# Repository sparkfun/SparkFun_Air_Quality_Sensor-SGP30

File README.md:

SparkFun Air Quality Sensor - SGP30 (Qwiic)
========================================

[*SparkFun Air Quality Sensor - SGP30 (Qwiic) (SEN-16531)*](https://www.sparkfun.com/products/16531)

The SGP30 is an Indoor Air Quality Sensor that outputs TVOC (in ppb) and CO<sub>2</sub> (in ppm) values along with raw measurements of H<sub>2</sub> and Ethanol.

Repository Contents
-------------------

* **/Hardware** - Eagle design files (.brd, .sch)
* **/Production** - Production panel files (.brd)

Documentation
--------------
* **[SGP30 Arduino Library](https://github.com/sparkfun/SparkFun_SGP30_Arduino_Library)** - Arduino library for the SparkFun Air Quality Sensor - SGP30.
* **[Hookup Guide](https://learn.sparkfun.com/tutorials/sparkfun-air-quality-sensor---sgp30-qwiic-hookup-guide)** - Basic hookup guide for the SparkFun Air Quality Sensor - SGP30. 
* **[SparkFun Fritzing repo](https://github.com/sparkfun/Fritzing_Parts)** - Fritzing diagrams for SparkFun products.
* **[SparkFun 3D Model repo](https://github.com/sparkfun/3D_Models)** - 3D models of SparkFun products.

Product Versions
----------------
* [SEN-16531](https://www.sparkfun.com/products/16531) - SparkFun initial release.
* [SPX-14813](https://www.sparkfun.com/products/14813) - Original SparkX Release.

License Information
-------------------

This product is _**open source**_! 

Please review the LICENSE.md file for license information. 

If you have any questions or concerns on licensing, please contact technical support on our [SparkFun forums](https://forum.sparkfun.com/viewforum.php?f=152).

Distributed as-is; no warranty is given.

- Your friends at SparkFun.

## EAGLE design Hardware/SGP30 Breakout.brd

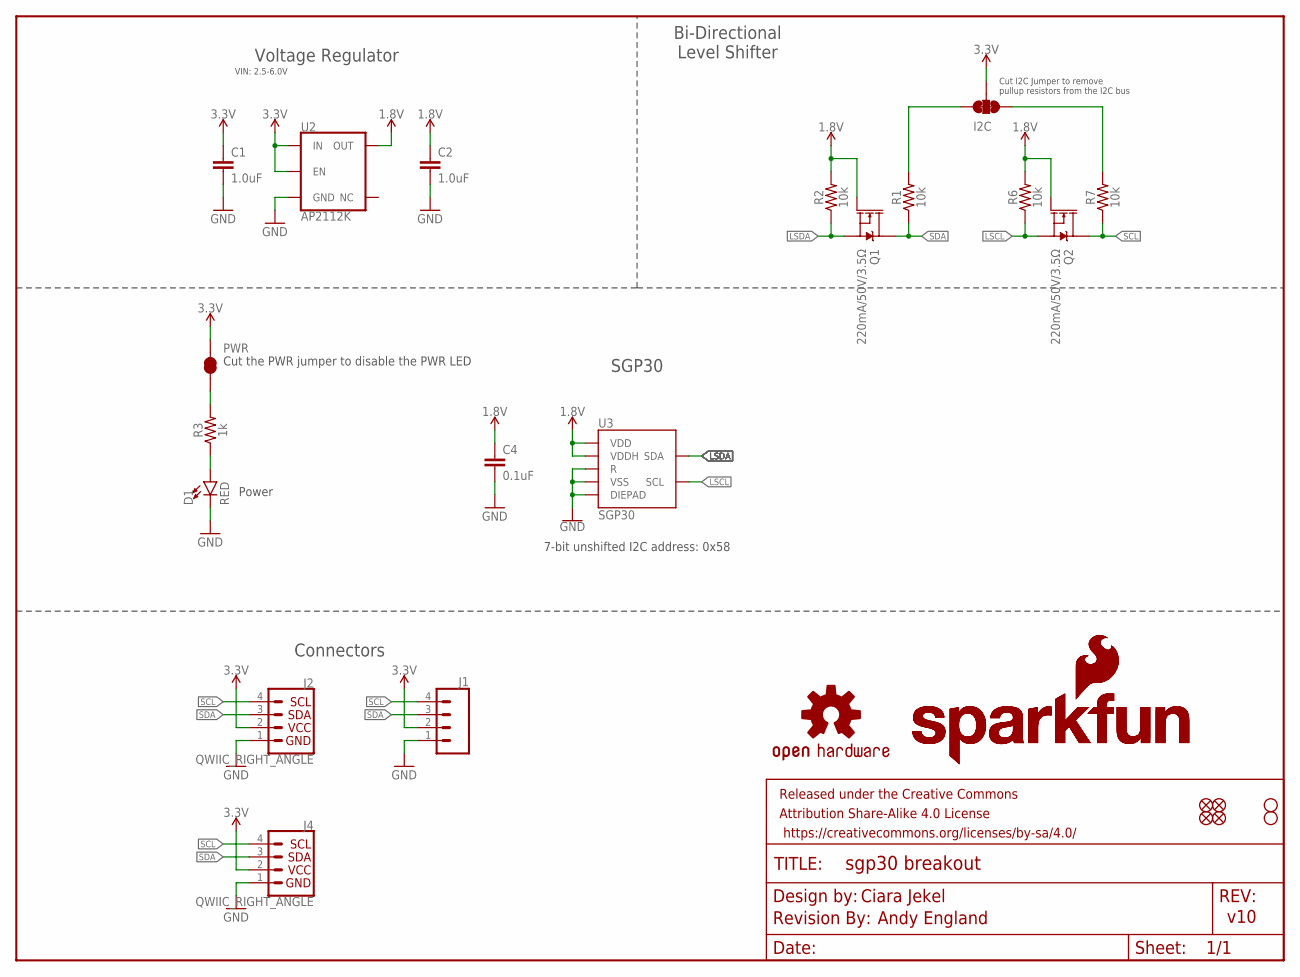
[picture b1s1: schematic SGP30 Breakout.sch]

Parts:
C1, C2: 1.0uF; 0603
C4: 0.1uF; 0603
D1: RED; LED-0603
FRAME1: FRAME-LETTER; CREATIVE_COMMONS
I2C: JUMPER-SMT_3_2-NC_TRACE_SILK; SMT-JUMPER_3_2-NC_TRACE_SILK
J1: CONN_041X04_NO_SILK; 1X04_NO_SILK
J2, J4: QWIIC_RIGHT_ANGLE; JST04_1MM_RA
JP1, JP2, JP5, JP6: FIDUCIALUFIDUCIAL; MICRO-FIDUCIAL
JP3, JP4: STAND-OFF
LOGO2: REVISION
LOGO3, LOGO4: SFE_LOGO_NAME_FLAME.1_INCH; SFE_LOGO_NAME_FLAME_.1
LOGO5: OSHW-LOGOS; OSHW-LOGO-S
PWR: JUMPER-SMT_2_NC_TRACE_SILK; SMT-JUMPER_2_NC_TRACE_SILK
Q1, Q2: 220mA/50V/3.5Ω; SOT23-3
R1, R2, R6, R7: 10k; 0603
R3: 1k; 0603
U2: AP2112K; SOT23-5
U3: SGP30

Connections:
1.8V: C2.1, C4.1, Q1.1 (G), Q2.1 (G), R2.2, R6.2, U2.5 (OUT), U3.1 (VDD), U3.5 (VDDH)
3.3V: C1.1, I2C.2, J1.2, J2.2, J4.2, PWR.2, U2.1 (IN), U2.3 (EN)
GND: C1.2, C2.2, C4.2, D1.C, J1.1, J2.1, J4.1, U2.2 (GND), U3.2 (VSS), U3.4 (R), U3.DIEPAD
LSCL: Q2.2 (S), R6.1, U3.6 (SCL)
LSDA: Q1.2 (S), R2.1, U3.3 (SDA)
unnamed: PWR.1, R3.2
unnamed: I2C.3, R1.2
unnamed: D1.A, R3.1
unnamed: I2C.1, R7.2
SCL: J1.4, J2.4, J4.4, Q2.3 (D), R7.1
SDA: J1.3, J2.3, J4.3, Q1.3 (D), R1.1

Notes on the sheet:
Ciara Jekel
v10
7-bit unshifted I2C address: 0x58
Power
Bi-Directional Level Shifter
Voltage Regulator
SGP30
Connectors
Cut the PWR jumper to disable the PWR LED
Andy England
VIN: 2.5-6.0V
Cut I2C Jumper to remove pullup resistors from the I2C bus

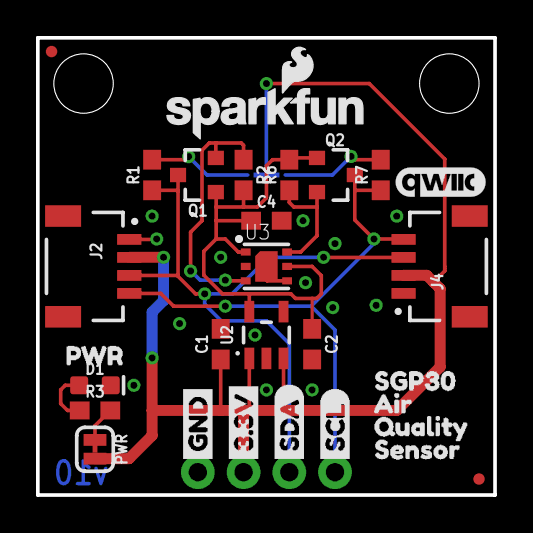
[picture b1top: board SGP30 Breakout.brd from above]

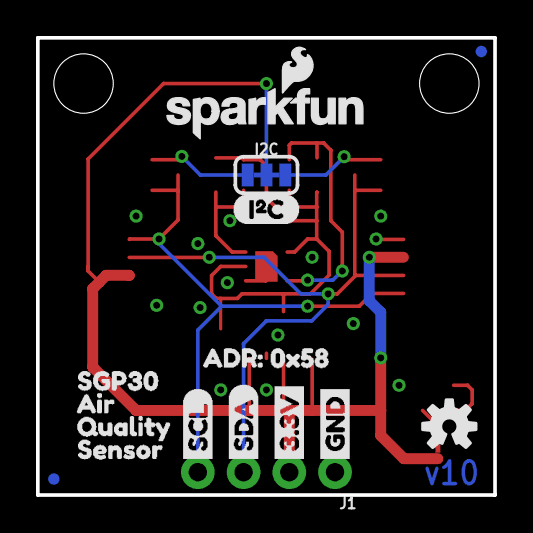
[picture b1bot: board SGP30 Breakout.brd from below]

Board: 2 copper layers, 25.4 x 25.4 mm, 49 parts (16 on the bottom side), 11 nets.

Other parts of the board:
U$1, U$11: _AIR1
U$2, U$12: QUALITY2
U$3, U$22: GND1
U$4, U$21: 3#3V2
U$5, U$27: SDA8
U$6, U$26: SCL9
U$7, U$13: SENSOR3
U$8, U$9: SGP300
U$14: ADR#_0X580
U$15: I2C
U$16: QWIIC_5MM
U$17: PWR_TO

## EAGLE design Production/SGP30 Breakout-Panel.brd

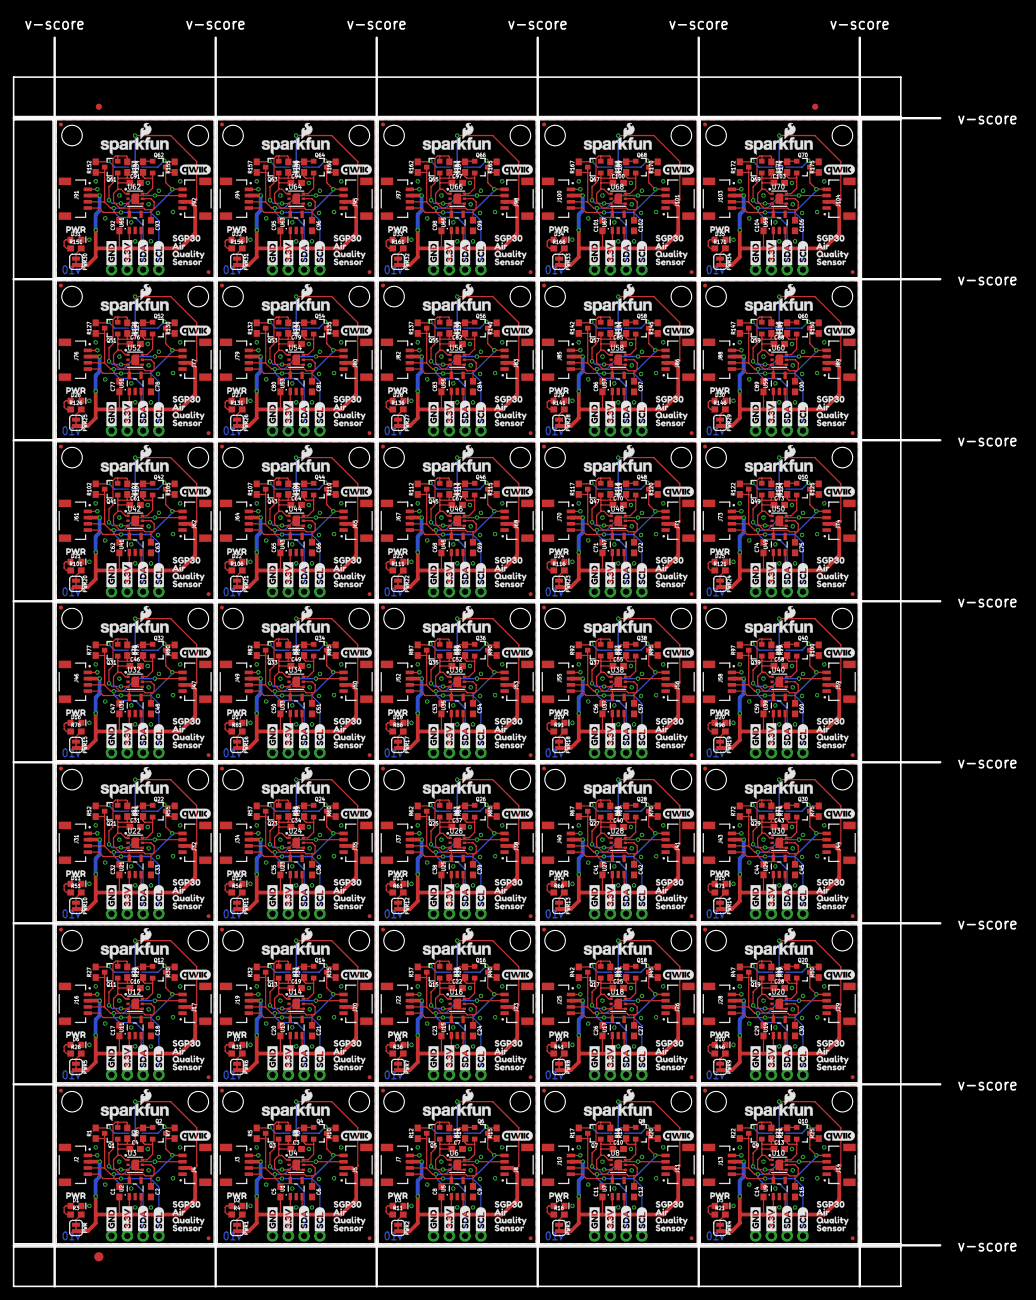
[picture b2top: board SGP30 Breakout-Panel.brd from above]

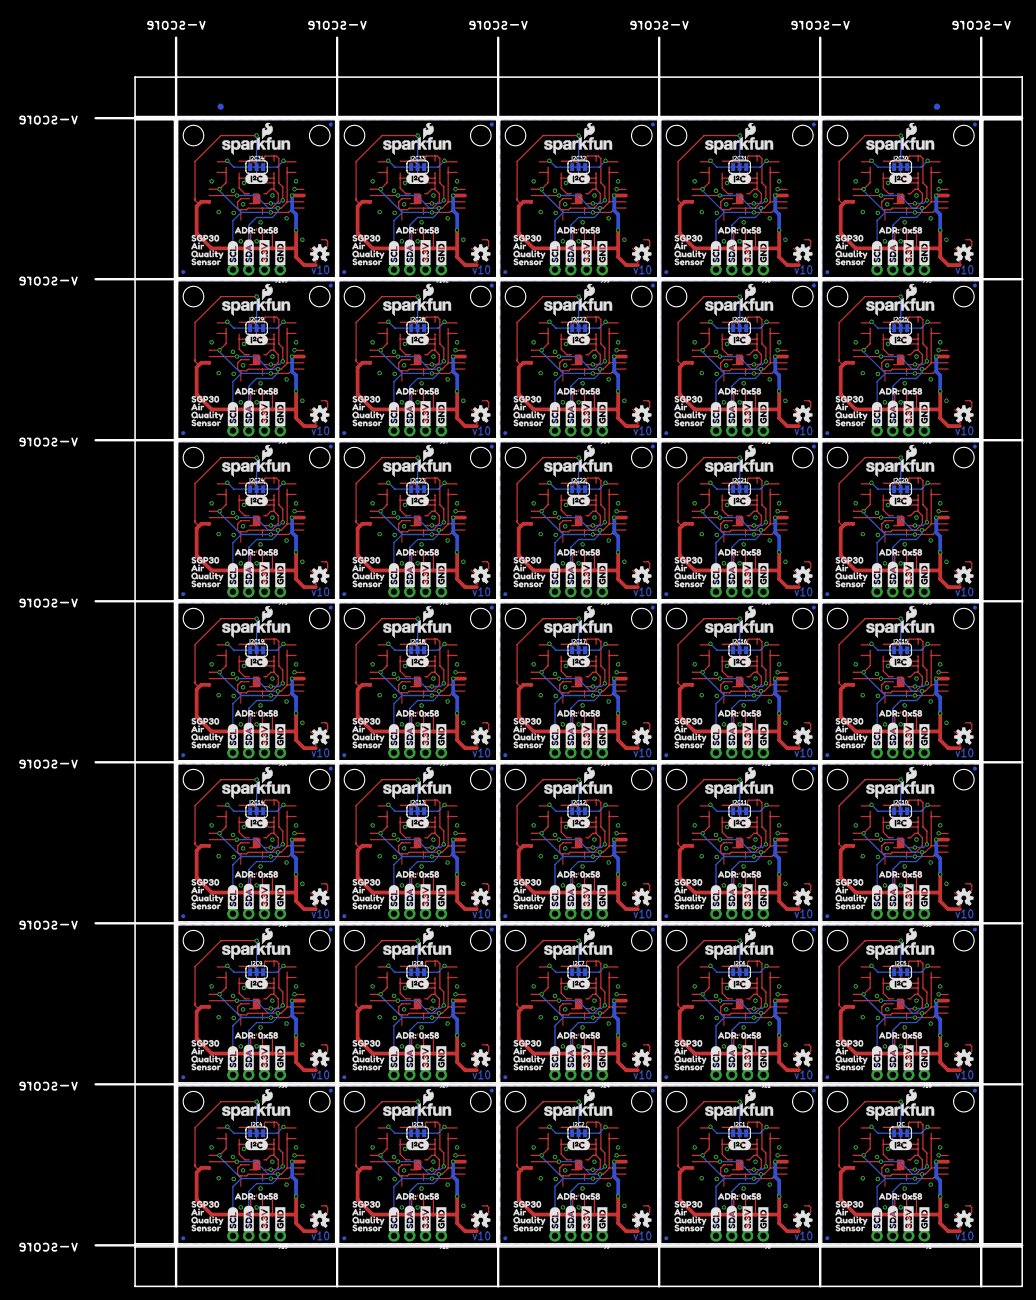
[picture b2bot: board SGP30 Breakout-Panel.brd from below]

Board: 2 copper layers, 149.1 x 200.9 mm, 1685 parts (562 on the bottom side), 385 nets.

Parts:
C1, C2, C5, C6, C8, C9, C11, C12, C14, C15, C17, C18, C20, C21, C23, C24, C26, C27, C29, C30, C32, C33, C35, C36, C38, C39, C41, C42, C44, C45, C47, C48, C50, C51, C53, C54, C56, C57, C59, C60, C62, C63, C65, C66, C68, C69, C71, C72, C74, C75, C77, C78, C80, C81, C83, C84, C86, C87, C89, C90, C92, C93, C95, C96, C98, C99, C101, C102, C104, C105: 1.0uF; 0603
C3, C4, C7, C10, C13, C16, C19, C22, C25, C28, C31, C34, C37, C40, C43, C46, C49, C52, C55, C58, C61, C64, C67, C70, C73, C76, C79, C82, C85, C88, C91, C94, C97, C100, C103: 0.1uF; 0603
D1, D2, D3, D4, D5, D6, D7, D8, D9, D10, D11, D12, D13, D14, D15, D16, D17, D18, D19, D20, D21, D22, D23, D24, D25, D26, D27, D28, D29, D30, D31, D32, D33, D34, D35: RED; LED-0603
E$1, E$2, E$3, E$4: FIDUCIAL-1X2
E$5: FIDUCIAL-1.5X3
I2C, I2C1, I2C2, I2C3, I2C4, I2C5, I2C6, I2C7, I2C8, I2C9, I2C10, I2C11, I2C12, I2C13, I2C14, I2C15, I2C16, I2C17, I2C18, I2C19, I2C20, I2C21, I2C22, I2C23, I2C24, I2C25, I2C26, I2C27, I2C28, I2C29, I2C30, I2C31, I2C32, I2C33, I2C34: JUMPER-SMT_3_2-NC_TRACE_SILK; SMT-JUMPER_3_2-NC_TRACE_SILK
J1, J6, J9, J12, J15, J18, J21, J24, J27, J30, J33, J36, J39, J42, J45, J48, J51, J54, J57, J60, J63, J66, J69, J72, J75, J78, J81, J84, J87, J90, J93, J96, J99, J102, J105: 1X04_NO_SILK
J2, J3, J4, J5, J7, J8, J10, J11, J13, J14, J16, J17, J19, J20, J22, J23, J25, J26, J28, J29, J31, J32, J34, J35, J37, J38, J40, J41, J43, J44, J46, J47, J49, J50, J52, J53, J55, J56, J58, J59, J61, J62, J64, J65, J67, J68, J70, J71, J73, J74, J76, J77, J79, J80, J82, J83, J85, J86, J88, J89, J91, J92, J94, J95, J97, J98, J100, J101, J103, J104: QWIIC_RIGHT_ANGLE; JST04_1MM_RA
JP1, JP2, JP5, JP6, JP9, JP10, JP11, JP12, JP15, JP16, JP17, JP18, JP21, JP22, JP23, JP24, JP27, JP28, JP29, JP30, JP33, JP34, JP35, JP36, JP39, JP40, JP41, JP42, JP45, JP46, JP47, JP48, JP51, JP52, JP53, JP54, JP57, JP58, JP59, JP60, JP63, JP64, JP65, JP66, JP69, JP70, JP71, JP72, JP75, JP76, JP77, JP78, JP81, JP82, JP83, JP84, JP87, JP88, JP89, JP90, JP93, JP94, JP95, JP96, JP99, JP100, JP101, JP102, JP105, JP106, JP107, JP108, JP111, JP112, JP113, JP114, JP117, JP118, JP119, JP120, JP123, JP124, JP125, JP126, JP129, JP130, JP131, JP132, JP135, JP136, JP137, JP138, JP141, JP142, JP143, JP144, JP147, JP148, JP149, JP150, JP153, JP154, JP155, JP156, JP159, JP160, JP161, JP162, JP165, JP166, JP167, JP168, JP171, JP172, JP173, JP174, JP177, JP178, JP179, JP180, JP183, JP184, JP185, JP186, JP189, JP190, JP191, JP192, JP195, JP196, JP197, JP198, JP201, JP202, JP203, JP204, JP207, JP208, JP209, JP210: FIDUCIALUFIDUCIAL; MICRO-FIDUCIAL
JP3, JP4, JP7, JP8, JP13, JP14, JP19, JP20, JP25, JP26, JP31, JP32, JP37, JP38, JP43, JP44, JP49, JP50, JP55, JP56, JP61, JP62, JP67, JP68, JP73, JP74, JP79, JP80, JP85, JP86, JP91, JP92, JP97, JP98, JP103, JP104, JP109, JP110, JP115, JP116, JP121, JP122, JP127, JP128, JP133, JP134, JP139, JP140, JP145, JP146, JP151, JP152, JP157, JP158, JP163, JP164, JP169, JP170, JP175, JP176, JP181, JP182, JP187, JP188, JP193, JP194, JP199, JP200, JP205, JP206: STAND-OFF
LOGO1, LOGO2, LOGO9, LOGO13, LOGO17, LOGO21, LOGO25, LOGO29, LOGO33, LOGO37, LOGO41, LOGO45, LOGO49, LOGO53, LOGO57, LOGO61, LOGO65, LOGO69, LOGO73, LOGO77, LOGO81, LOGO85, LOGO89, LOGO93, LOGO97, LOGO101, LOGO105, LOGO109, LOGO113, LOGO117, LOGO121, LOGO125, LOGO129, LOGO133, LOGO137: REVISION
LOGO3, LOGO4, LOGO6, LOGO7, LOGO10, LOGO11, LOGO14, LOGO15, LOGO18, LOGO19, LOGO22, LOGO23, LOGO26, LOGO27, LOGO30, LOGO31, LOGO34, LOGO35, LOGO38, LOGO39, LOGO42, LOGO43, LOGO46, LOGO47, LOGO50, LOGO51, LOGO54, LOGO55, LOGO58, LOGO59, LOGO62, LOGO63, LOGO66, LOGO67, LOGO70, LOGO71, LOGO74, LOGO75, LOGO78, LOGO79, LOGO82, LOGO83, LOGO86, LOGO87, LOGO90, LOGO91, LOGO94, LOGO95, LOGO98, LOGO99, LOGO102, LOGO103, LOGO106, LOGO107, LOGO110, LOGO111, LOGO114, LOGO115, LOGO118, LOGO119, LOGO122, LOGO123, LOGO126, LOGO127, LOGO130, LOGO131, LOGO134, LOGO135, LOGO138, LOGO139: SFE_LOGO_NAME_FLAME.1_INCH; SFE_LOGO_NAME_FLAME_.1
LOGO5, LOGO8, LOGO12, LOGO16, LOGO20, LOGO24, LOGO28, LOGO32, LOGO36, LOGO40, LOGO44, LOGO48, LOGO52, LOGO56, LOGO60, LOGO64, LOGO68, LOGO72, LOGO76, LOGO80, LOGO84, LOGO88, LOGO92, LOGO96, LOGO100, LOGO104, LOGO108, LOGO112, LOGO116, LOGO120, LOGO124, LOGO128, LOGO132, LOGO136, LOGO140: OSHW-LOGOS; OSHW-LOGO-S
PWR, PWR1, PWR2, PWR3, PWR4, PWR5, PWR6, PWR7, PWR8, PWR9, PWR10, PWR11, PWR12, PWR13, PWR14, PWR15, PWR16, PWR17, PWR18, PWR19, PWR20, PWR21, PWR22, PWR23, PWR24, PWR25, PWR26, PWR27, PWR28, PWR29, PWR30, PWR31, PWR32, PWR33, PWR34: JUMPER-SMT_2_NC_TRACE_SILK; SMT-JUMPER_2_NC_TRACE_SILK
Q1, Q2, Q3, Q4, Q5, Q6, Q7, Q8, Q9, Q10, Q11, Q12, Q13, Q14, Q15, Q16, Q17, Q18, Q19, Q20, Q21, Q22, Q23, Q24, Q25, Q26, Q27, Q28, Q29, Q30, Q31, Q32, Q33, Q34, Q35, Q36, Q37, Q38, Q39, Q40, Q41, Q42, Q43, Q44, Q45, Q46, Q47, Q48, Q49, Q50, Q51, Q52, Q53, Q54, Q55, Q56, Q57, Q58, Q59, Q60, Q61, Q62, Q63, Q64, Q65, Q66, Q67, Q68, Q69, Q70: 220mA/50V/3.5Ω; SOT23-3
R1, R2, R5, R6, R7, R8, R9, R10, R12, R13, R14, R15, R17, R18, R19, R20, R22, R23, R24, R25, R27, R28, R29, R30, R32, R33, R34, R35, R37, R38, R39, R40, R42, R43, R44, R45, R47, R48, R49, R50, R52, R53, R54, R55, R57, R58, R59, R60, R62, R63, R64, R65, R67, R68, R69, R70, R72, R73, R74, R75, R77, R78, R79, R80, R82, R83, R84, R85, R87, R88, R89, R90, R92, R93, R94, R95, R97, R98, R99, R100, R102, R103, R104, R105, R107, R108, R109, R110, R112, R113, R114, R115, R117, R118, R119, R120, R122, R123, R124, R125, R127, R128, R129, R130, R132, R133, R134, R135, R137, R138, R139, R140, R142, R143, R144, R145, R147, R148, R149, R150, R152, R153, R154, R155, R157, R158, R159, R160, R162, R163, R164, R165, R167, R168, R169, R170, R172, R173, R174, R175: 10k; 0603
R3, R4, R11, R16, R21, R26, R31, R36, R41, R46, R51, R56, R61, R66, R71, R76, R81, R86, R91, R96, R101, R106, R111, R116, R121, R126, R131, R136, R141, R146, R151, R156, R161, R166, R171: 1k; 0603
U1, U2, U5, U7, U9, U11, U13, U15, U17, U19, U21, U23, U25, U27, U29, U31, U33, U35, U37, U39, U41, U43, U45, U47, U49, U51, U53, U55, U57, U59, U61, U63, U65, U67, U69: AP2112K; SOT23-5
U3, U4, U6, U8, U10, U12, U14, U16, U18, U20, U22, U24, U26, U28, U30, U32, U34, U36, U38, U40, U42, U44, U46, U48, U50, U52, U54, U56, U58, U60, U62, U64, U66, U68, U70: SGP30
U$1, U$11, U$29, U$34, U$49, U$54, U$69, U$74, U$89, U$94, U$109, U$114, U$129, U$134, U$149, U$154, U$169, U$174, U$189, U$194, U$209, U$214, U$229, U$234, U$249, U$254, U$269, U$274, U$289, U$294, U$309, U$314, U$329, U$334, U$349, U$354, U$369, U$374, U$389, U$394, U$409, U$414, U$429, U$434, U$449, U$454, U$469, U$474, U$489, U$494, U$509, U$514, U$529, U$534, U$549, U$554, U$569, U$574, U$589, U$594, U$609, U$614, U$629, U$634, U$649, U$654, U$669, U$674, U$689, U$694: _AIR1
U$2, U$12, U$30, U$35, U$50, U$55, U$70, U$75, U$90, U$95, U$110, U$115, U$130, U$135, U$150, U$155, U$170, U$175, U$190, U$195, U$210, U$215, U$230, U$235, U$250, U$255, U$270, U$275, U$290, U$295, U$310, U$315, U$330, U$335, U$350, U$355, U$370, U$375, U$390, U$395, U$410, U$415, U$430, U$435, U$450, U$455, U$470, U$475, U$490, U$495, U$510, U$515, U$530, U$535, U$550, U$555, U$570, U$575, U$590, U$595, U$610, U$615, U$630, U$635, U$650, U$655, U$670, U$675, U$690, U$695: QUALITY2
U$3, U$18, U$22, U$23, U$42, U$45, U$62, U$65, U$82, U$85, U$102, U$105, U$122, U$125, U$142, U$145, U$162, U$165, U$182, U$185, U$202, U$205, U$222, U$225, U$242, U$245, U$262, U$265, U$282, U$285, U$302, U$305, U$322, U$325, U$342, U$345, U$362, U$365, U$382, U$385, U$402, U$405, U$422, U$425, U$442, U$445, U$462, U$465, U$482, U$485, U$502, U$505, U$522, U$525, U$542, U$545, U$562, U$565, U$582, U$585, U$602, U$605, U$622, U$625, U$642, U$645, U$662, U$665, U$682, U$685: GND1
U$4, U$10, U$21, U$24, U$41, U$46, U$61, U$66, U$81, U$86, U$101, U$106, U$121, U$126, U$141, U$146, U$161, U$166, U$181, U$186, U$201, U$206, U$221, U$226, U$241, U$246, U$261, U$266, U$281, U$286, U$301, U$306, U$321, U$326, U$341, U$346, U$361, U$366, U$381, U$386, U$401, U$406, U$421, U$426, U$441, U$446, U$461, U$466, U$481, U$486, U$501, U$506, U$521, U$526, U$541, U$546, U$561, U$566, U$581, U$586, U$601, U$606, U$621, U$626, U$641, U$646, U$661, U$666, U$681, U$686: 3#3V2
U$5, U$20, U$25, U$27, U$44, U$47, U$64, U$67, U$84, U$87, U$104, U$107, U$124, U$127, U$144, U$147, U$164, U$167, U$184, U$187, U$204, U$207, U$224, U$227, U$244, U$247, U$264, U$267, U$284, U$287, U$304, U$307, U$324, U$327, U$344, U$347, U$364, U$367, U$384, U$387, U$404, U$407, U$424, U$427, U$444, U$447, U$464, U$467, U$484, U$487, U$504, U$507, U$524, U$527, U$544, U$547, U$564, U$567, U$584, U$587, U$604, U$607, U$624, U$627, U$644, U$647, U$664, U$667, U$684, U$687: SDA8
U$6, U$19, U$26, U$28, U$43, U$48, U$63, U$68, U$83, U$88, U$103, U$108, U$123, U$128, U$143, U$148, U$163, U$168, U$183, U$188, U$203, U$208, U$223, U$228, U$243, U$248, U$263, U$268, U$283, U$288, U$303, U$308, U$323, U$328, U$343, U$348, U$363, U$368, U$383, U$388, U$403, U$408, U$423, U$428, U$443, U$448, U$463, U$468, U$483, U$488, U$503, U$508, U$523, U$528, U$543, U$548, U$563, U$568, U$583, U$588, U$603, U$608, U$623, U$628, U$643, U$648, U$663, U$668, U$683, U$688: SCL9
U$7, U$13, U$31, U$36, U$51, U$56, U$71, U$76, U$91, U$96, U$111, U$116, U$131, U$136, U$151, U$156, U$171, U$176, U$191, U$196, U$211, U$216, U$231, U$236, U$251, U$256, U$271, U$276, U$291, U$296, U$311, U$316, U$331, U$336, U$351, U$356, U$371, U$376, U$391, U$396, U$411, U$416, U$431, U$436, U$451, U$456, U$471, U$476, U$491, U$496, U$511, U$516, U$531, U$536, U$551, U$556, U$571, U$576, U$591, U$596, U$611, U$616, U$631, U$636, U$651, U$656, U$671, U$676, U$691, U$696: SENSOR3
U$8, U$9, U$32, U$33, U$52, U$53, U$72, U$73, U$92, U$93, U$112, U$113, U$132, U$133, U$152, U$153, U$172, U$173, U$192, U$193, U$212, U$213, U$232, U$233, U$252, U$253, U$272, U$273, U$292, U$293, U$312, U$313, U$332, U$333, U$352, U$353, U$372, U$373, U$392, U$393, U$412, U$413, U$432, U$433, U$452, U$453, U$472, U$473, U$492, U$493, U$512, U$513, U$532, U$533, U$552, U$553, U$572, U$573, U$592, U$593, U$612, U$613, U$632, U$633, U$652, U$653, U$672, U$673, U$692, U$693: SGP300
U$14, U$37, U$57, U$77, U$97, U$117, U$137, U$157, U$177, U$197, U$217, U$237, U$257, U$277, U$297, U$317, U$337, U$357, U$377, U$397, U$417, U$437, U$457, U$477, U$497, U$517, U$537, U$557, U$577, U$597, U$617, U$637, U$657, U$677, U$697: ADR#_0X580
U$15, U$38, U$58, U$78, U$98, U$118, U$138, U$158, U$178, U$198, U$218, U$238, U$258, U$278, U$298, U$318, U$338, U$358, U$378, U$398, U$418, U$438, U$458, U$478, U$498, U$518, U$538, U$558, U$578, U$598, U$618, U$638, U$658, U$678, U$698: I2C
U$16, U$39, U$59, U$79, U$99, U$119, U$139, U$159, U$179, U$199, U$219, U$239, U$259, U$279, U$299, U$319, U$339, U$359, U$379, U$399, U$419, U$439, U$459, U$479, U$499, U$519, U$539, U$559, U$579, U$599, U$619, U$639, U$659, U$679, U$699: QWIIC_5MM
U$17, U$40, U$60, U$80, U$100, U$120, U$140, U$160, U$180, U$200, U$220, U$240, U$260, U$280, U$300, U$320, U$340, U$360, U$380, U$400, U$420, U$440, U$460, U$480, U$500, U$520, U$540, U$560, U$580, U$600, U$620, U$640, U$660, U$680, U$700: PWR_TO

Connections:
1.8V: C2.1, C4.1, Q1.1, Q2.1, R2.2, R6.2, U2.5, U3.1, U3.5
1.8V1: C3.1, C6.1, Q3.1, Q4.1, R8.2, R9.2, U1.5, U4.1, U4.5
1.8V2: C7.1, C9.1, Q5.1, Q6.1, R13.2, R14.2, U5.5, U6.1, U6.5
1.8V3: C10.1, C12.1, Q7.1, Q8.1, R18.2, R19.2, U7.5, U8.1, U8.5
1.8V4: C13.1, C15.1, Q9.1, Q10.1, R23.2, R24.2, U9.5, U10.1, U10.5
1.8V5: C16.1, C18.1, Q11.1, Q12.1, R28.2, R29.2, U11.5, U12.1, U12.5
1.8V6: C19.1, C21.1, Q13.1, Q14.1, R33.2, R34.2, U13.5, U14.1, U14.5
1.8V7: C22.1, C24.1, Q15.1, Q16.1, R38.2, R39.2, U15.5, U16.1, U16.5
1.8V8: C25.1, C27.1, Q17.1, Q18.1, R43.2, R44.2, U17.5, U18.1, U18.5
1.8V9: C28.1, C30.1, Q19.1, Q20.1, R48.2, R49.2, U19.5, U20.1, U20.5
1.8V10: C31.1, C33.1, Q21.1, Q22.1, R53.2, R54.2, U21.5, U22.1, U22.5
1.8V11: C34.1, C36.1, Q23.1, Q24.1, R58.2, R59.2, U23.5, U24.1, U24.5
1.8V12: C37.1, C39.1, Q25.1, Q26.1, R63.2, R64.2, U25.5, U26.1, U26.5
1.8V13: C40.1, C42.1, Q27.1, Q28.1, R68.2, R69.2, U27.5, U28.1, U28.5
1.8V14: C43.1, C45.1, Q29.1, Q30.1, R73.2, R74.2, U29.5, U30.1, U30.5
1.8V15: C46.1, C48.1, Q31.1, Q32.1, R78.2, R79.2, U31.5, U32.1, U32.5
1.8V16: C49.1, C51.1, Q33.1, Q34.1, R83.2, R84.2, U33.5, U34.1, U34.5
1.8V17: C52.1, C54.1, Q35.1, Q36.1, R88.2, R89.2, U35.5, U36.1, U36.5
1.8V18: C55.1, C57.1, Q37.1, Q38.1, R93.2, R94.2, U37.5, U38.1, U38.5
1.8V19: C58.1, C60.1, Q39.1, Q40.1, R98.2, R99.2, U39.5, U40.1, U40.5
1.8V20: C61.1, C63.1, Q41.1, Q42.1, R103.2, R104.2, U41.5, U42.1, U42.5
1.8V21: C64.1, C66.1, Q43.1, Q44.1, R108.2, R109.2, U43.5, U44.1, U44.5
1.8V22: C67.1, C69.1, Q45.1, Q46.1, R113.2, R114.2, U45.5, U46.1, U46.5
1.8V23: C70.1, C72.1, Q47.1, Q48.1, R118.2, R119.2, U47.5, U48.1, U48.5
1.8V24: C73.1, C75.1, Q49.1, Q50.1, R123.2, R124.2, U49.5, U50.1, U50.5
1.8V25: C76.1, C78.1, Q51.1, Q52.1, R128.2, R129.2, U51.5, U52.1, U52.5
1.8V26: C79.1, C81.1, Q53.1, Q54.1, R133.2, R134.2, U53.5, U54.1, U54.5
1.8V27: C82.1, C84.1, Q55.1, Q56.1, R138.2, R139.2, U55.5, U56.1, U56.5
1.8V28: C85.1, C87.1, Q57.1, Q58.1, R143.2, R144.2, U57.5, U58.1, U58.5
1.8V29: C88.1, C90.1, Q59.1, Q60.1, R148.2, R149.2, U59.5, U60.1, U60.5
1.8V30: C91.1, C93.1, Q61.1, Q62.1, R153.2, R154.2, U61.5, U62.1, U62.5
1.8V31: C94.1, C96.1, Q63.1, Q64.1, R158.2, R159.2, U63.5, U64.1, U64.5
1.8V32: C97.1, C99.1, Q65.1, Q66.1, R163.2, R164.2, U65.5, U66.1, U66.5
1.8V33: C100.1, C102.1, Q67.1, Q68.1, R168.2, R169.2, U67.5, U68.1, U68.5
1.8V34: C103.1, C105.1, Q69.1, Q70.1, R173.2, R174.2, U69.5, U70.1, U70.5
3.3V: C1.1, I2C.2, J1.2, J2.2, J4.2, PWR.2, U2.1, U2.3
3.3V1: C5.1, I2C1.2, J3.2, J5.2, J6.2, PWR1.2, U1.1, U1.3
3.3V2: C8.1, I2C2.2, J7.2, J8.2, J9.2, PWR2.2, U5.1, U5.3
3.3V3: C11.1, I2C3.2, J10.2, J11.2, J12.2, PWR3.2, U7.1, U7.3
3.3V4: C14.1, I2C4.2, J13.2, J14.2, J15.2, PWR4.2, U9.1, U9.3
3.3V5: C17.1, I2C5.2, J16.2, J17.2, J18.2, PWR5.2, U11.1, U11.3
3.3V6: C20.1, I2C6.2, J19.2, J20.2, J21.2, PWR6.2, U13.1, U13.3
3.3V7: C23.1, I2C7.2, J22.2, J23.2, J24.2, PWR7.2, U15.1, U15.3
3.3V8: C26.1, I2C8.2, J25.2, J26.2, J27.2, PWR8.2, U17.1, U17.3
3.3V9: C29.1, I2C9.2, J28.2, J29.2, J30.2, PWR9.2, U19.1, U19.3
3.3V10: C32.1, I2C10.2, J31.2, J32.2, J33.2, PWR10.2, U21.1, U21.3
3.3V11: C35.1, I2C11.2, J34.2, J35.2, J36.2, PWR11.2, U23.1, U23.3
3.3V12: C38.1, I2C12.2, J37.2, J38.2, J39.2, PWR12.2, U25.1, U25.3
3.3V13: C41.1, I2C13.2, J40.2, J41.2, J42.2, PWR13.2, U27.1, U27.3
3.3V14: C44.1, I2C14.2, J43.2, J44.2, J45.2, PWR14.2, U29.1, U29.3
3.3V15: C47.1, I2C15.2, J46.2, J47.2, J48.2, PWR15.2, U31.1, U31.3
3.3V16: C50.1, I2C16.2, J49.2, J50.2, J51.2, PWR16.2, U33.1, U33.3
3.3V17: C53.1, I2C17.2, J52.2, J53.2, J54.2, PWR17.2, U35.1, U35.3
3.3V18: C56.1, I2C18.2, J55.2, J56.2, J57.2, PWR18.2, U37.1, U37.3
3.3V19: C59.1, I2C19.2, J58.2, J59.2, J60.2, PWR19.2, U39.1, U39.3
3.3V20: C62.1, I2C20.2, J61.2, J62.2, J63.2, PWR20.2, U41.1, U41.3
3.3V21: C65.1, I2C21.2, J64.2, J65.2, J66.2, PWR21.2, U43.1, U43.3
3.3V22: C68.1, I2C22.2, J67.2, J68.2, J69.2, PWR22.2, U45.1, U45.3
3.3V23: C71.1, I2C23.2, J70.2, J71.2, J72.2, PWR23.2, U47.1, U47.3
3.3V24: C74.1, I2C24.2, J73.2, J74.2, J75.2, PWR24.2, U49.1, U49.3
3.3V25: C77.1, I2C25.2, J76.2, J77.2, J78.2, PWR25.2, U51.1, U51.3
3.3V26: C80.1, I2C26.2, J79.2, J80.2, J81.2, PWR26.2, U53.1, U53.3
3.3V27: C83.1, I2C27.2, J82.2, J83.2, J84.2, PWR27.2, U55.1, U55.3
3.3V28: C86.1, I2C28.2, J85.2, J86.2, J87.2, PWR28.2, U57.1, U57.3
3.3V29: C89.1, I2C29.2, J88.2, J89.2, J90.2, PWR29.2, U59.1, U59.3
3.3V30: C92.1, I2C30.2, J91.2, J92.2, J93.2, PWR30.2, U61.1, U61.3
3.3V31: C95.1, I2C31.2, J94.2, J95.2, J96.2, PWR31.2, U63.1, U63.3
3.3V32: C98.1, I2C32.2, J97.2, J98.2, J99.2, PWR32.2, U65.1, U65.3
3.3V33: C101.1, I2C33.2, J100.2, J101.2, J102.2, PWR33.2, U67.1, U67.3
3.3V34: C104.1, I2C34.2, J103.2, J104.2, J105.2, PWR34.2, U69.1, U69.3
GND: C1.2, C2.2, C4.2, D1.C, J1.1, J2.1, J4.1, U2.2, U3.2, U3.4, U3.DIEPAD
GND1: C3.2, C5.2, C6.2, D2.C, J3.1, J5.1, J6.1, U1.2, U4.2, U4.4, U4.DIEPAD
GND2: C7.2, C8.2, C9.2, D3.C, J7.1, J8.1, J9.1, U5.2, U6.2, U6.4, U6.DIEPAD
GND3: C10.2, C11.2, C12.2, D4.C, J10.1, J11.1, J12.1, U7.2, U8.2, U8.4, U8.DIEPAD
GND4: C13.2, C14.2, C15.2, D5.C, J13.1, J14.1, J15.1, U9.2, U10.2, U10.4, U10.DIEPAD
GND5: C16.2, C17.2, C18.2, D6.C, J16.1, J17.1, J18.1, U11.2, U12.2, U12.4, U12.DIEPAD
GND6: C19.2, C20.2, C21.2, D7.C, J19.1, J20.1, J21.1, U13.2, U14.2, U14.4, U14.DIEPAD
GND7: C22.2, C23.2, C24.2, D8.C, J22.1, J23.1, J24.1, U15.2, U16.2, U16.4, U16.DIEPAD
GND8: C25.2, C26.2, C27.2, D9.C, J25.1, J26.1, J27.1, U17.2, U18.2, U18.4, U18.DIEPAD
GND9: C28.2, C29.2, C30.2, D10.C, J28.1, J29.1, J30.1, U19.2, U20.2, U20.4, U20.DIEPAD
GND10: C31.2, C32.2, C33.2, D11.C, J31.1, J32.1, J33.1, U21.2, U22.2, U22.4, U22.DIEPAD
GND11: C34.2, C35.2, C36.2, D12.C, J34.1, J35.1, J36.1, U23.2, U24.2, U24.4, U24.DIEPAD
GND12: C37.2, C38.2, C39.2, D13.C, J37.1, J38.1, J39.1, U25.2, U26.2, U26.4, U26.DIEPAD
GND13: C40.2, C41.2, C42.2, D14.C, J40.1, J41.1, J42.1, U27.2, U28.2, U28.4, U28.DIEPAD
GND14: C43.2, C44.2, C45.2, D15.C, J43.1, J44.1, J45.1, U29.2, U30.2, U30.4, U30.DIEPAD
GND15: C46.2, C47.2, C48.2, D16.C, J46.1, J47.1, J48.1, U31.2, U32.2, U32.4, U32.DIEPAD
GND16: C49.2, C50.2, C51.2, D17.C, J49.1, J50.1, J51.1, U33.2, U34.2, U34.4, U34.DIEPAD
GND17: C52.2, C53.2, C54.2, D18.C, J52.1, J53.1, J54.1, U35.2, U36.2, U36.4, U36.DIEPAD
GND18: C55.2, C56.2, C57.2, D19.C, J55.1, J56.1, J57.1, U37.2, U38.2, U38.4, U38.DIEPAD
GND19: C58.2, C59.2, C60.2, D20.C, J58.1, J59.1, J60.1, U39.2, U40.2, U40.4, U40.DIEPAD
GND20: C61.2, C62.2, C63.2, D21.C, J61.1, J62.1, J63.1, U41.2, U42.2, U42.4, U42.DIEPAD
GND21: C64.2, C65.2, C66.2, D22.C, J64.1, J65.1, J66.1, U43.2, U44.2, U44.4, U44.DIEPAD
GND22: C67.2, C68.2, C69.2, D23.C, J67.1, J68.1, J69.1, U45.2, U46.2, U46.4, U46.DIEPAD
GND23: C70.2, C71.2, C72.2, D24.C, J70.1, J71.1, J72.1, U47.2, U48.2, U48.4, U48.DIEPAD
GND24: C73.2, C74.2, C75.2, D25.C, J73.1, J74.1, J75.1, U49.2, U50.2, U50.4, U50.DIEPAD
GND25: C76.2, C77.2, C78.2, D26.C, J76.1, J77.1, J78.1, U51.2, U52.2, U52.4, U52.DIEPAD
GND26: C79.2, C80.2, C81.2, D27.C, J79.1, J80.1, J81.1, U53.2, U54.2, U54.4, U54.DIEPAD
GND27: C82.2, C83.2, C84.2, D28.C, J82.1, J83.1, J84.1, U55.2, U56.2, U56.4, U56.DIEPAD
GND28: C85.2, C86.2, C87.2, D29.C, J85.1, J86.1, J87.1, U57.2, U58.2, U58.4, U58.DIEPAD
GND29: C88.2, C89.2, C90.2, D30.C, J88.1, J89.1, J90.1, U59.2, U60.2, U60.4, U60.DIEPAD
GND30: C91.2, C92.2, C93.2, D31.C, J91.1, J92.1, J93.1, U61.2, U62.2, U62.4, U62.DIEPAD
GND31: C94.2, C95.2, C96.2, D32.C, J94.1, J95.1, J96.1, U63.2, U64.2, U64.4, U64.DIEPAD
GND32: C97.2, C98.2, C99.2, D33.C, J97.1, J98.1, J99.1, U65.2, U66.2, U66.4, U66.DIEPAD
GND33: C100.2, C101.2, C102.2, D34.C, J100.1, J101.1, J102.1, U67.2, U68.2, U68.4, U68.DIEPAD
GND34: C103.2, C104.2, C105.2, D35.C, J103.1, J104.1, J105.1, U69.2, U70.2, U70.4, U70.DIEPAD
LSCL: Q2.2, R6.1, U3.6
LSCL1: Q4.2, R9.1, U4.6
LSCL2: Q6.2, R14.1, U6.6
LSCL3: Q8.2, R19.1, U8.6
LSCL4: Q10.2, R24.1, U10.6
LSCL5: Q12.2, R29.1, U12.6
LSCL6: Q14.2, R34.1, U14.6
LSCL7: Q16.2, R39.1, U16.6
LSCL8: Q18.2, R44.1, U18.6
LSCL9: Q20.2, R49.1, U20.6
LSCL10: Q22.2, R54.1, U22.6
LSCL11: Q24.2, R59.1, U24.6
LSCL12: Q26.2, R64.1, U26.6
LSCL13: Q28.2, R69.1, U28.6
LSCL14: Q30.2, R74.1, U30.6
LSCL15: Q32.2, R79.1, U32.6
LSCL16: Q34.2, R84.1, U34.6
LSCL17: Q36.2, R89.1, U36.6
LSCL18: Q38.2, R94.1, U38.6
LSCL19: Q40.2, R99.1, U40.6
LSCL20: Q42.2, R104.1, U42.6
LSCL21: Q44.2, R109.1, U44.6
LSCL22: Q46.2, R114.1, U46.6
LSCL23: Q48.2, R119.1, U48.6
LSCL24: Q50.2, R124.1, U50.6
LSCL25: Q52.2, R129.1, U52.6
LSCL26: Q54.2, R134.1, U54.6
LSCL27: Q56.2, R139.1, U56.6
LSCL28: Q58.2, R144.1, U58.6
LSCL29: Q60.2, R149.1, U60.6
LSCL30: Q62.2, R154.1, U62.6
LSCL31: Q64.2, R159.1, U64.6
LSCL32: Q66.2, R164.1, U66.6
LSCL33: Q68.2, R169.1, U68.6
LSCL34: Q70.2, R174.1, U70.6
LSDA: Q1.2, R2.1, U3.3
LSDA1: Q3.2, R8.1, U4.3
LSDA2: Q5.2, R13.1, U6.3
LSDA3: Q7.2, R18.1, U8.3
LSDA4: Q9.2, R23.1, U10.3
LSDA5: Q11.2, R28.1, U12.3
LSDA6: Q13.2, R33.1, U14.3
LSDA7: Q15.2, R38.1, U16.3
LSDA8: Q17.2, R43.1, U18.3
LSDA9: Q19.2, R48.1, U20.3
LSDA10: Q21.2, R53.1, U22.3
LSDA11: Q23.2, R58.1, U24.3
LSDA12: Q25.2, R63.1, U26.3
LSDA13: Q27.2, R68.1, U28.3
LSDA14: Q29.2, R73.1, U30.3
LSDA15: Q31.2, R78.1, U32.3
LSDA16: Q33.2, R83.1, U34.3
LSDA17: Q35.2, R88.1, U36.3
LSDA18: Q37.2, R93.1, U38.3
LSDA19: Q39.2, R98.1, U40.3
LSDA20: Q41.2, R103.1, U42.3
LSDA21: Q43.2, R108.1, U44.3
LSDA22: Q45.2, R113.1, U46.3
LSDA23: Q47.2, R118.1, U48.3
LSDA24: Q49.2, R123.1, U50.3
LSDA25: Q51.2, R128.1, U52.3
LSDA26: Q53.2, R133.1, U54.3
LSDA27: Q55.2, R138.1, U56.3
LSDA28: Q57.2, R143.1, U58.3
LSDA29: Q59.2, R148.1, U60.3
LSDA30: Q61.2, R153.1, U62.3
LSDA31: Q63.2, R158.1, U64.3
LSDA32: Q65.2, R163.1, U66.3
LSDA33: Q67.2, R168.1, U68.3
LSDA34: Q69.2, R173.1, U70.3
unnamed: PWR.1, R3.2
unnamed: I2C.3, R1.2
unnamed: D1.A, R3.1
unnamed: I2C.1, R7.2
unnamed: D2.A, R4.1
unnamed: PWR1.1, R4.2
unnamed: I2C1.3, R5.2
unnamed: I2C1.1, R10.2
unnamed: D3.A, R11.1
unnamed: PWR2.1, R11.2
unnamed: I2C2.3, R12.2
unnamed: I2C2.1, R15.2
unnamed: D4.A, R16.1
unnamed: PWR3.1, R16.2
unnamed: I2C3.3, R17.2
unnamed: I2C3.1, R20.2
unnamed: D5.A, R21.1
unnamed: PWR4.1, R21.2
unnamed: I2C4.3, R22.2
unnamed: I2C4.1, R25.2
unnamed: D6.A, R26.1
unnamed: PWR5.1, R26.2
unnamed: I2C5.3, R27.2
unnamed: I2C5.1, R30.2
unnamed: D7.A, R31.1
unnamed: PWR6.1, R31.2
unnamed: I2C6.3, R32.2
unnamed: I2C6.1, R35.2
unnamed: D8.A, R36.1
unnamed: PWR7.1, R36.2
unnamed: I2C7.3, R37.2
unnamed: I2C7.1, R40.2
unnamed: D9.A, R41.1
unnamed: PWR8.1, R41.2
unnamed: I2C8.3, R42.2
unnamed: I2C8.1, R45.2
unnamed: D10.A, R46.1
unnamed: PWR9.1, R46.2
unnamed: I2C9.3, R47.2
unnamed: I2C9.1, R50.2
unnamed: D11.A, R51.1
unnamed: PWR10.1, R51.2
unnamed: I2C10.3, R52.2
unnamed: I2C10.1, R55.2
unnamed: D12.A, R56.1
unnamed: PWR11.1, R56.2
unnamed: I2C11.3, R57.2
unnamed: I2C11.1, R60.2
unnamed: D13.A, R61.1
unnamed: PWR12.1, R61.2
unnamed: I2C12.3, R62.2
unnamed: I2C12.1, R65.2
unnamed: D14.A, R66.1
unnamed: PWR13.1, R66.2
unnamed: I2C13.3, R67.2
unnamed: I2C13.1, R70.2
unnamed: D15.A, R71.1
unnamed: PWR14.1, R71.2
unnamed: I2C14.3, R72.2
unnamed: I2C14.1, R75.2
unnamed: D16.A, R76.1
unnamed: PWR15.1, R76.2
unnamed: I2C15.3, R77.2
unnamed: I2C15.1, R80.2
unnamed: D17.A, R81.1
unnamed: PWR16.1, R81.2
unnamed: I2C16.3, R82.2
unnamed: I2C16.1, R85.2
unnamed: D18.A, R86.1
unnamed: PWR17.1, R86.2
unnamed: I2C17.3, R87.2
unnamed: I2C17.1, R90.2
unnamed: D19.A, R91.1
unnamed: PWR18.1, R91.2
unnamed: I2C18.3, R92.2
unnamed: I2C18.1, R95.2
unnamed: D20.A, R96.1
unnamed: PWR19.1, R96.2
unnamed: I2C19.3, R97.2
unnamed: I2C19.1, R100.2
unnamed: D21.A, R101.1
unnamed: PWR20.1, R101.2
unnamed: I2C20.3, R102.2
unnamed: I2C20.1, R105.2
unnamed: D22.A, R106.1
unnamed: PWR21.1, R106.2
unnamed: I2C21.3, R107.2
unnamed: I2C21.1, R110.2
unnamed: D23.A, R111.1
unnamed: PWR22.1, R111.2
unnamed: I2C22.3, R112.2
unnamed: I2C22.1, R115.2
unnamed: D24.A, R116.1
unnamed: PWR23.1, R116.2
unnamed: I2C23.3, R117.2
unnamed: I2C23.1, R120.2
unnamed: D25.A, R121.1
unnamed: PWR24.1, R121.2
unnamed: I2C24.3, R122.2
unnamed: I2C24.1, R125.2
unnamed: D26.A, R126.1
unnamed: PWR25.1, R126.2
unnamed: I2C25.3, R127.2
unnamed: I2C25.1, R130.2
unnamed: D27.A, R131.1
unnamed: PWR26.1, R131.2
unnamed: I2C26.3, R132.2
unnamed: I2C26.1, R135.2
unnamed: D28.A, R136.1
unnamed: PWR27.1, R136.2
unnamed: I2C27.3, R137.2
unnamed: I2C27.1, R140.2
unnamed: D29.A, R141.1
unnamed: PWR28.1, R141.2
unnamed: I2C28.3, R142.2
unnamed: I2C28.1, R145.2
unnamed: D30.A, R146.1
unnamed: PWR29.1, R146.2
unnamed: I2C29.3, R147.2
unnamed: I2C29.1, R150.2
unnamed: D31.A, R151.1
unnamed: PWR30.1, R151.2
unnamed: I2C30.3, R152.2
unnamed: I2C30.1, R155.2
unnamed: D32.A, R156.1
unnamed: PWR31.1, R156.2
unnamed: I2C31.3, R157.2
unnamed: I2C31.1, R160.2
unnamed: D33.A, R161.1
unnamed: PWR32.1, R161.2
unnamed: I2C32.3, R162.2
unnamed: I2C32.1, R165.2
unnamed: D34.A, R166.1
unnamed: PWR33.1, R166.2
unnamed: I2C33.3, R167.2
unnamed: I2C33.1, R170.2
unnamed: D35.A, R171.1
unnamed: PWR34.1, R171.2
unnamed: I2C34.3, R172.2
unnamed: I2C34.1, R175.2
SCL: J1.4, J2.4, J4.4, Q2.3, R7.1
SCL1: J3.4, J5.4, J6.4, Q4.3, R10.1
SCL2: J7.4, J8.4, J9.4, Q6.3, R15.1
SCL3: J10.4, J11.4, J12.4, Q8.3, R20.1
SCL4: J13.4, J14.4, J15.4, Q10.3, R25.1
SCL5: J16.4, J17.4, J18.4, Q12.3, R30.1
SCL6: J19.4, J20.4, J21.4, Q14.3, R35.1
SCL7: J22.4, J23.4, J24.4, Q16.3, R40.1
SCL8: J25.4, J26.4, J27.4, Q18.3, R45.1
SCL9: J28.4, J29.4, J30.4, Q20.3, R50.1
SCL10: J31.4, J32.4, J33.4, Q22.3, R55.1
SCL11: J34.4, J35.4, J36.4, Q24.3, R60.1
SCL12: J37.4, J38.4, J39.4, Q26.3, R65.1
SCL13: J40.4, J41.4, J42.4, Q28.3, R70.1
SCL14: J43.4, J44.4, J45.4, Q30.3, R75.1
SCL15: J46.4, J47.4, J48.4, Q32.3, R80.1
SCL16: J49.4, J50.4, J51.4, Q34.3, R85.1
SCL17: J52.4, J53.4, J54.4, Q36.3, R90.1
SCL18: J55.4, J56.4, J57.4, Q38.3, R95.1
SCL19: J58.4, J59.4, J60.4, Q40.3, R100.1
SCL20: J61.4, J62.4, J63.4, Q42.3, R105.1
SCL21: J64.4, J65.4, J66.4, Q44.3, R110.1
SCL22: J67.4, J68.4, J69.4, Q46.3, R115.1
SCL23: J70.4, J71.4, J72.4, Q48.3, R120.1
SCL24: J73.4, J74.4, J75.4, Q50.3, R125.1
SCL25: J76.4, J77.4, J78.4, Q52.3, R130.1
SCL26: J79.4, J80.4, J81.4, Q54.3, R135.1
SCL27: J82.4, J83.4, J84.4, Q56.3, R140.1
SCL28: J85.4, J86.4, J87.4, Q58.3, R145.1
SCL29: J88.4, J89.4, J90.4, Q60.3, R150.1
SCL30: J91.4, J92.4, J93.4, Q62.3, R155.1
SCL31: J94.4, J95.4, J96.4, Q64.3, R160.1
SCL32: J97.4, J98.4, J99.4, Q66.3, R165.1
SCL33: J100.4, J101.4, J102.4, Q68.3, R170.1
SCL34: J103.4, J104.4, J105.4, Q70.3, R175.1
SDA: J1.3, J2.3, J4.3, Q1.3, R1.1
SDA1: J3.3, J5.3, J6.3, Q3.3, R5.1
SDA2: J7.3, J8.3, J9.3, Q5.3, R12.1
SDA3: J10.3, J11.3, J12.3, Q7.3, R17.1
SDA4: J13.3, J14.3, J15.3, Q9.3, R22.1
SDA5: J16.3, J17.3, J18.3, Q11.3, R27.1
SDA6: J19.3, J20.3, J21.3, Q13.3, R32.1
SDA7: J22.3, J23.3, J24.3, Q15.3, R37.1
SDA8: J25.3, J26.3, J27.3, Q17.3, R42.1
SDA9: J28.3, J29.3, J30.3, Q19.3, R47.1
SDA10: J31.3, J32.3, J33.3, Q21.3, R52.1
SDA11: J34.3, J35.3, J36.3, Q23.3, R57.1
SDA12: J37.3, J38.3, J39.3, Q25.3, R62.1
SDA13: J40.3, J41.3, J42.3, Q27.3, R67.1
SDA14: J43.3, J44.3, J45.3, Q29.3, R72.1
SDA15: J46.3, J47.3, J48.3, Q31.3, R77.1
SDA16: J49.3, J50.3, J51.3, Q33.3, R82.1
SDA17: J52.3, J53.3, J54.3, Q35.3, R87.1
SDA18: J55.3, J56.3, J57.3, Q37.3, R92.1
SDA19: J58.3, J59.3, J60.3, Q39.3, R97.1
SDA20: J61.3, J62.3, J63.3, Q41.3, R102.1
SDA21: J64.3, J65.3, J66.3, Q43.3, R107.1
SDA22: J67.3, J68.3, J69.3, Q45.3, R112.1
SDA23: J70.3, J71.3, J72.3, Q47.3, R117.1
SDA24: J73.3, J74.3, J75.3, Q49.3, R122.1
SDA25: J76.3, J77.3, J78.3, Q51.3, R127.1
SDA26: J79.3, J80.3, J81.3, Q53.3, R132.1
SDA27: J82.3, J83.3, J84.3, Q55.3, R137.1
SDA28: J85.3, J86.3, J87.3, Q57.3, R142.1
SDA29: J88.3, J89.3, J90.3, Q59.3, R147.1
SDA30: J91.3, J92.3, J93.3, Q61.3, R152.1
SDA31: J94.3, J95.3, J96.3, Q63.3, R157.1
SDA32: J97.3, J98.3, J99.3, Q65.3, R162.1
SDA33: J100.3, J101.3, J102.3, Q67.3, R167.1
SDA34: J103.3, J104.3, J105.3, Q69.3, R172.1

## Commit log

2020-04-06 pre-review changes
2020-04-07 Post review/checklist changes
2020-04-08 post qc-double check
2020-04-08 adding panel
2020-04-08 moving production folder out to root
2020-06-03 Create README.md
    Initial commit of README file.
2020-10-30 replacing 3.3V VREG with 1.8V in Schematic
2020-10-30 fixing brd/sch inconsistency

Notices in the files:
parts and their libraries:
SparkFun-Resistors: Licensing: Creative Commons ShareAlike 4.0 International - https://creativecommons.org/licenses/by-sa/4.0
SparkFun-Aesthetics: Released under the Creative Commons Attribution Share-Alike 4.0 License
SparkFun-Aesthetics: https://creativecommons.org/licenses/by-sa/4.0
